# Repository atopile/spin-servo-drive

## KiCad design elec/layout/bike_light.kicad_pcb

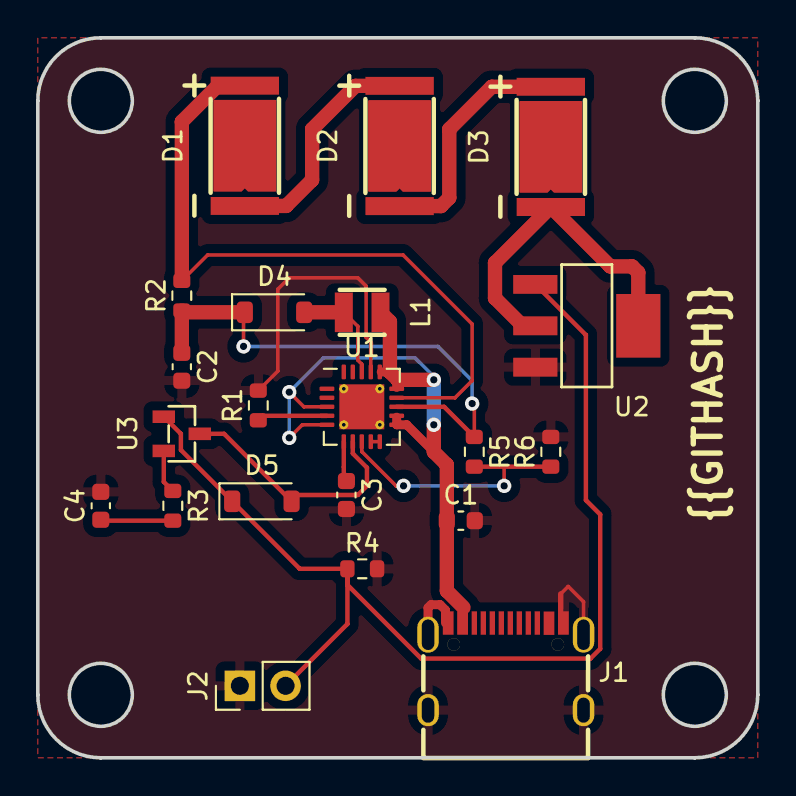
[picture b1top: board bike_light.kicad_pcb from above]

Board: 2 copper layers, 40.0 x 40.0 mm, 21 parts (0 on the bottom side), 20 nets.

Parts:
C1: 3.3uF; C_0603_1608Metric
C2: 10uF; C_0603_1608Metric
C3: 33nF; C_0603_1608Metric
C4: 10nF; C_0603_1608Metric
D1, D2, D3: LED-SMD_3P-L7.0-W3.5_XL-C3570P5S10-62C3C2
D4, D5: D_SOD-123
J1: USB-C-SMD_KH-TYPE-C-16P
J2: PinHeader_1x02_P2.54mm_Vertical
L1: 2uH; IND-SMD_L2.5-W2.0_SLW252012P
R1: 6.81k; R_0603_1608Metric
R2: 0.33R; R_0603_1608Metric
R3: 2.4k; R_0603_1608Metric
R4: 100k; R_0603_1608Metric
R5: 1M; R_0603_1608Metric
R6: 75k; R_0603_1608Metric
U1: QFN-20-1EP_4x4mm_P0.5mm_EP2.5x2.5mm_ThermalVias
U2: SOT-223_L6.5-W3.5-P2.30-LS7.0-BR
U3: SOT-23-3_L2.9-W1.3-P1.90-LS2.4-BR

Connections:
1: C1.1, J1.A4, J1.A9, J1.B4, J1.B9, L1.1, U1.3, U1.5, U1.11, U1.12, U1.15, U1.16
2: C1.2, C2.2, C3.2, C4.2, J1.1, J1.2, J1.3, J1.4, J1.A1, J1.A12, J1.B1, J1.B12, J2.1, R1.2, R4.2, R6.2, U1.17, U2.3
4: D1.1, D2.3
5: D1.3, R2.2, U1.14
7: D2.1, D3.3
9: D3.1, U2.2, U2.4
11: C2.1, D4.1, R2.1, R5.1, U1.13
12: D5.1, J2.2, R4.1, U2.1, U3.1
14: R1.1, U1.4
15: C3.1, U1.6
16: D5.2, U1.7, U3.3
17: R5.2, R6.1, U1.8
18: U1.9, U1.10
19: D4.2, L1.2, U1.18
29: R3.1, U3.2
31: C4.1, R3.2
38: J1.A6, J1.B6
39: J1.A7, J1.B7
40: J1.A5, J1.B5
41: J1.A8, J1.B8

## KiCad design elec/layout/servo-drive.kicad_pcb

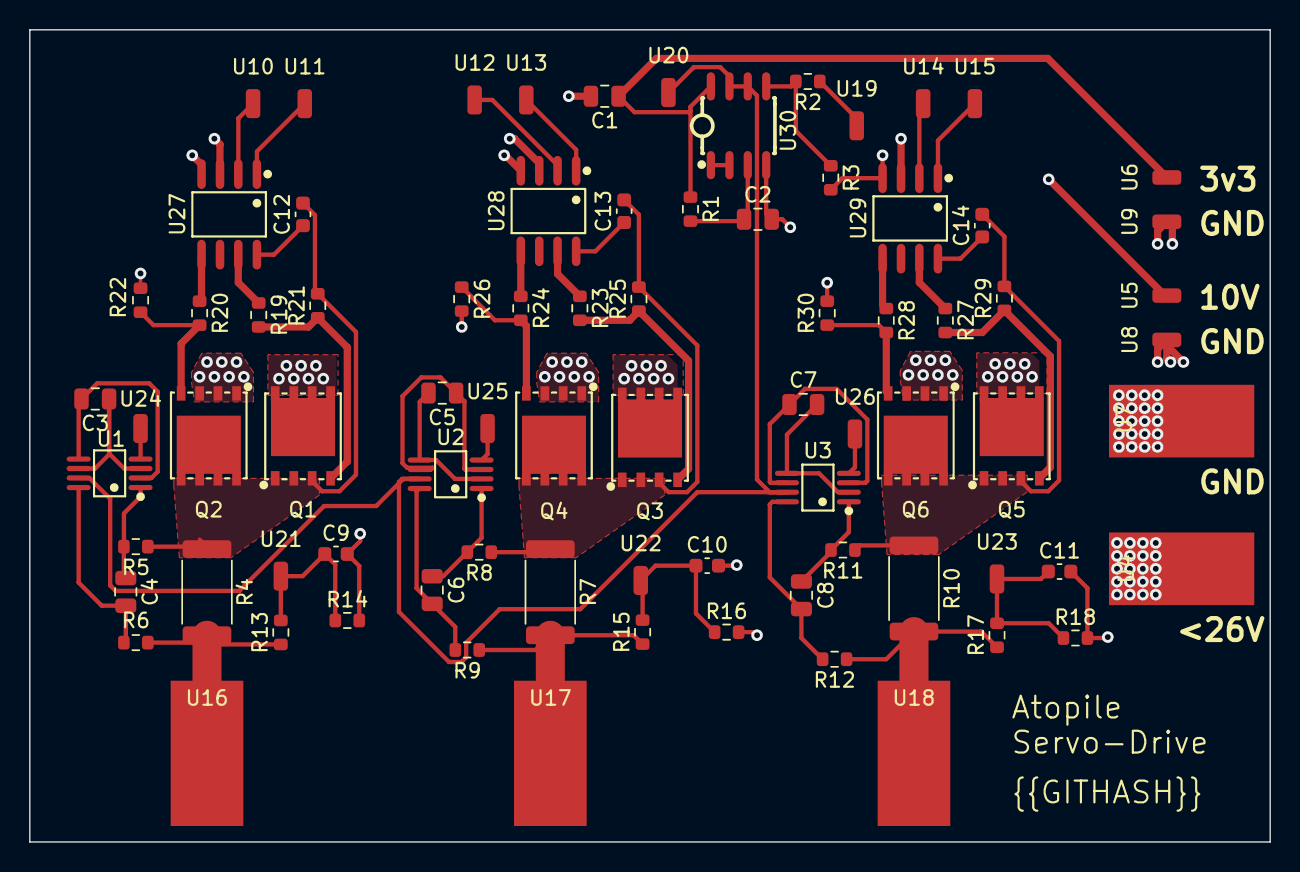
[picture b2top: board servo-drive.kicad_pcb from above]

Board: 4 copper layers, 85.3 x 55.9 mm, 80 parts (0 on the bottom side), 54 nets.

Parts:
C1, C2, C3, C4, C5, C6, C7, C8: 1uF; C_0805_2012Metric
C9, C10, C11: 2nF; C_0603_1608Metric
C12, C13, C14: 0.1uF; C_0603_1608Metric
Q1, Q2, Q3, Q4, Q5, Q6: DFN-8_L5.9-W5.2-P1.27-LS6.2-BL
R1, R2, R3, R13, R15, R17, R21, R22, R25, R26, R29, R30: 10kOhm; R_0603_1608Metric
R4, R7, R10: 1mOhm; R_2512_6332Metric
R5, R6, R8, R9, R11, R12: 10ohm; R_0603_1608Metric
R14, R16, R18: 1kOhm; R_0603_1608Metric
R19, R20, R23, R24, R27, R28: 25ohm; R_0603_1608Metric
U1, U2, U3: VSSOP-8_L3.0-W3.0-P0.65-LS5.0-BL
U4, U7, U16, U17, U18: SolderWirePad_1x01_SMD_5x10mm
U5, U6, U8, U9, U10, U11, U12, U13, U14, U15, U19, U20, U21, U22, U23, U24, U25, U26: SolderWirePad_1x01_SMD_1x2mm
U27, U28, U29: SOIC-8_L4.9-W3.9-P1.27-LS6.0-BL
U30: SOIC-8_L5.0-W4.0-P1.27-LS6.0-BL

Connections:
2: Q1.5, Q1.6, Q1.7, Q1.8, Q1.9, Q3.5, Q3.6, Q3.7, Q3.8, Q3.9, Q5.5, Q5.6, Q5.7, Q5.8, Q5.9, U4.1
3: U5.1, U27.3, U28.3, U29.3
4: C1.1, R1.1, U6.1, U30.8
5: C1.2, C2.2, C9.2, C10.2, C11.2, Q2.1, Q2.2, Q2.3, Q4.1, Q4.2, Q4.3, Q6.1, Q6.2, Q6.3, R3.2, R14.2, R16.2, R18.2, R22.2, R26.2, R30.2, U7.1, U8.1, U9.1, U27.4, U28.4, U29.4, U30.4
6: U10.1, U27.2
7: U11.1, U27.1
8: U12.1, U28.2
9: U13.1, U28.1
10: U14.1, U29.2
11: U15.1, U29.1
12: R4.2, R6.1, R13.1, U16.1
13: R7.2, R9.1, R15.1, U17.1
14: R10.2, R12.1, R17.1, U18.1
15: R2.1, U19.1
16: U1.7, U2.7, U3.7, U20.1, U30.6, U30.7
17: C9.1, R13.2, R14.1, U21.1
18: C10.1, R15.2, R16.1, U22.1
19: C11.1, R17.2, R18.1, U23.1
20: U1.4, U24.1
21: U2.4, U25.1
22: U3.4, U26.1
24: C12.2, Q1.1, Q1.2, Q1.3, Q2.5, Q2.6, Q2.7, Q2.8, Q2.9, R4.1, R5.1, R21.2
26: R19.1, U27.7
27: C12.1, U27.8
29: R20.1, U27.5
31: Q1.4, R19.2, R21.1
33: Q2.4, R20.2, R22.1
40: C13.2, Q3.1, Q3.2, Q3.3, Q4.5, Q4.6, Q4.7, Q4.8, Q4.9, R7.1, R8.1, R25.2
42: R23.1, U28.7
43: C13.1, U28.8
45: R24.1, U28.5
47: Q3.4, R23.2, R25.1
49: Q4.4, R24.2, R26.1
56: C14.2, Q5.1, Q5.2, Q5.3, Q6.5, Q6.6, Q6.7, Q6.8, Q6.9, R10.1, R11.1, R29.2
58: R27.1, U29.7
59: C14.1, U29.8
61: R28.1, U29.5
63: Q5.4, R27.2, R29.1
65: Q6.4, R28.2, R30.1
73: C2.1, R1.2, U30.3
74: U30.1, U30.2
75: R2.2, R3.1, U30.5
84: C3.1, U1.3, U1.6
85: C3.2, U1.2, U1.5
88: C4.1, R5.2, U1.1
89: C4.2, R6.2, U1.8
95: C5.1, U2.3, U2.6
96: C5.2, U2.2, U2.5
99: C6.1, R8.2, U2.1
100: C6.2, R9.2, U2.8
106: C7.1, U3.3, U3.6
107: C7.2, U3.2, U3.5
110: C8.1, R11.2, U3.1
111: C8.2, R12.2, U3.8
